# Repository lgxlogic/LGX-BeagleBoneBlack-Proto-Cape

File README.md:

BeagleBone Black Proto Cape
===========================

This repository contains the Eagle design files for the LGX Proto Cape for the BeagleBone Black.  

Check out the LGX Proto Cape at http://www.logicsupply.com/products/cbb_proto  

**NOTE**: On CBB-Proto r01 the **SYS5V** and **VDD5V** labels are reversed. This is only
a concern if drawing higher currents from the 5V rail, or when supplying power 
to the BeagleBone through the proto cape instead of the DC barrel jack. In 
both cases the bus labelled **SYS5V** should be used, as it is connected directly 
to the BeagleBone's DC input.  

----

Follow us on Google+ for updates and more information: https://plus.google.com/u/0/b/103613886667848850929/

Created by Alexander Hiam for LGX / Logic Supply.

Creative Commons Attribution 3.0 Unported License.  
To view a copy of this license,visit http://creativecommons.org/licenses/by/3.0/.  
All text above must be included in any redistribution.

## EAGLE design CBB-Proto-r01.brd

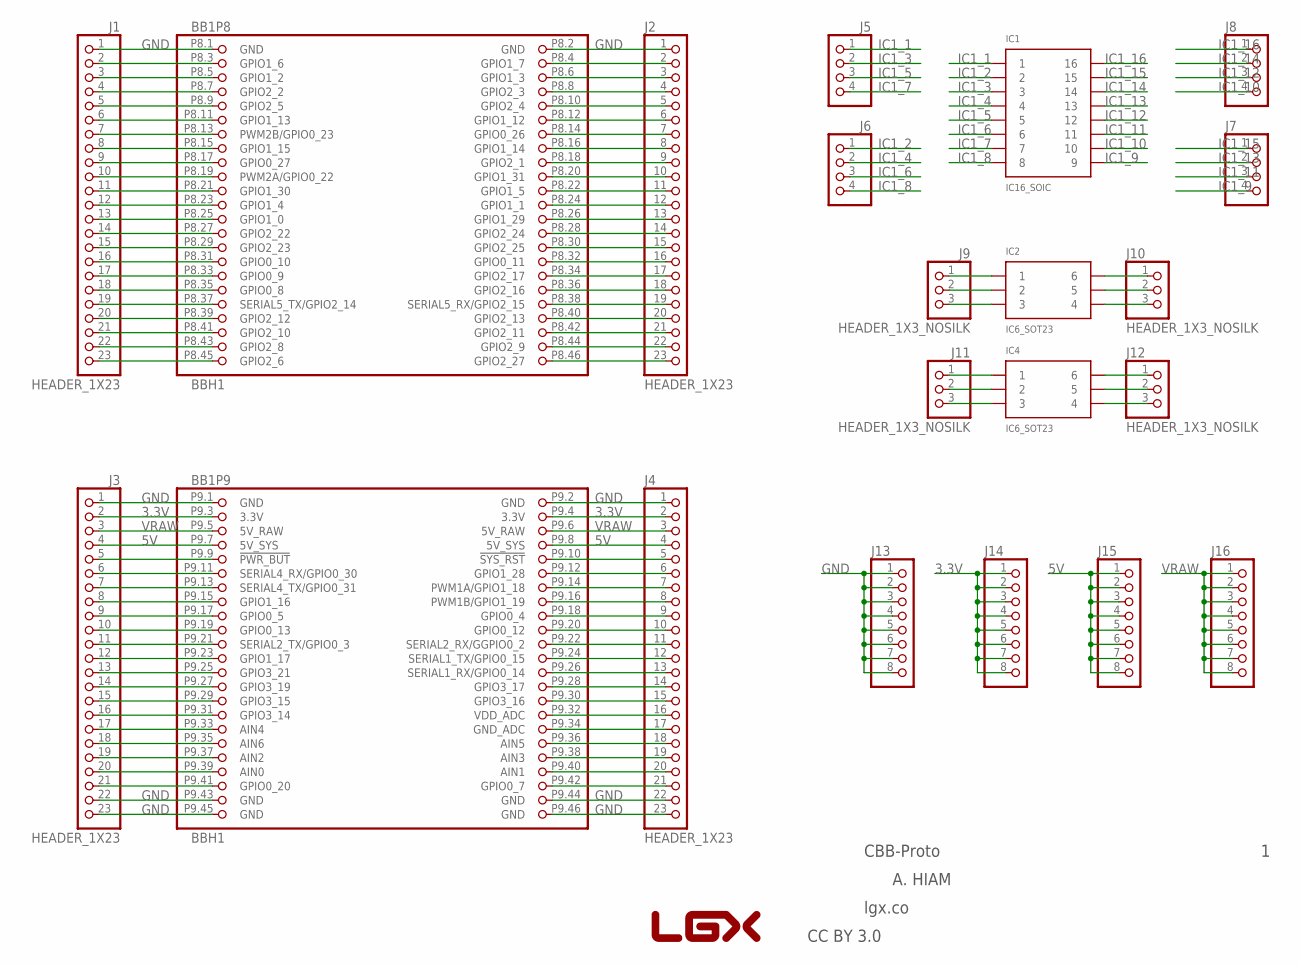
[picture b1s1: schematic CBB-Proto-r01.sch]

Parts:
BB1: BBH1; BB_CAPE
IC1: IC16_SOIC; SOIC16
IC2, IC4: IC6_SOT23; SOT23-6
J1, J2, J3, J4: HEADER_1X23
J5, J6, J7, J8: HEADER_1X4
J9, J10, J11, J12: HEADER_1X3_NOSILK
J13, J14, J15, J16: HEADER_1X8
U$1: LOGO-LGX

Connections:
3.3V: BB1.P9.3 (3.3V), BB1.P9.4 (3.3V), J3.2, J4.2, J14.1, J14.2, J14.3, J14.4, J14.5, J14.6, J14.7, J14.8
5V: BB1.P9.7 (5V_SYS), BB1.P9.8 (5V_SYS), J3.4, J4.4, J15.1, J15.2, J15.3, J15.4, J15.5, J15.6, J15.7, J15.8
GND: BB1.P8.1 (GND), BB1.P8.2 (GND), BB1.P9.1 (GND), BB1.P9.2 (GND), BB1.P9.43 (GND), BB1.P9.44 (GND), BB1.P9.45 (GND), BB1.P9.46 (GND), J1.1, J2.1, J3.1, J3.22, J3.23, J4.1, J4.22, J4.23, J13.1, J13.2, J13.3, J13.4, J13.5, J13.6, J13.7, J13.8
IC1_1: IC1.1, J5.1
IC1_2: IC1.2, J6.1
IC1_3: IC1.3, J5.2
IC1_4: IC1.4, J6.2
IC1_5: IC1.5, J5.3
IC1_6: IC1.6, J6.3
IC1_7: IC1.7, J5.4
IC1_8: IC1.8, J6.4
IC1_9: IC1.9, J7.4
IC1_10: IC1.10, J8.4
IC1_11: IC1.11, J7.3
IC1_12: IC1.12, J8.3
IC1_13: IC1.13, J7.2
IC1_14: IC1.14, J8.2
IC1_15: IC1.15, J7.1
IC1_16: IC1.16, J8.1
unnamed: BB1.P8.4 (GPIO1_7), J2.2
unnamed: BB1.P8.6 (GPIO1_3), J2.3
unnamed: BB1.P8.8 (GPIO2_3), J2.4
unnamed: BB1.P8.10 (GPIO2_4), J2.5
unnamed: BB1.P8.12 (GPIO1_12), J2.6
unnamed: BB1.P8.14 (GPIO0_26), J2.7
unnamed: BB1.P8.16 (GPIO1_14), J2.8
unnamed: BB1.P8.18 (GPIO2_1), J2.9
unnamed: BB1.P8.20 (GPIO1_31), J2.10
unnamed: BB1.P8.22 (GPIO1_5), J2.11
unnamed: BB1.P8.24 (GPIO1_1), J2.12
unnamed: BB1.P8.26 (GPIO1_29), J2.13
unnamed: BB1.P8.28 (GPIO2_24), J2.14
unnamed: BB1.P8.30 (GPIO2_25), J2.15
unnamed: BB1.P8.32 (GPIO0_11), J2.16
unnamed: BB1.P8.34 (GPIO2_17), J2.17
unnamed: BB1.P8.36 (GPIO2_16), J2.18
unnamed: BB1.P8.38 (SERIAL5_RX/GPIO2_15), J2.19
unnamed: BB1.P8.40 (GPIO2_13), J2.20
unnamed: BB1.P8.42 (GPIO2_11), J2.21
unnamed: BB1.P8.44 (GPIO2_9), J2.22
unnamed: BB1.P8.46 (GPIO2_27), J2.23
unnamed: BB1.P8.45 (GPIO2_6), J1.23
unnamed: BB1.P8.43 (GPIO2_8), J1.22
unnamed: BB1.P8.41 (GPIO2_10), J1.21
unnamed: BB1.P8.39 (GPIO2_12), J1.20
unnamed: BB1.P8.37 (SERIAL5_TX/GPIO2_14), J1.19
unnamed: BB1.P8.35 (GPIO0_8), J1.18
unnamed: BB1.P8.33 (GPIO0_9), J1.17
unnamed: BB1.P8.31 (GPIO0_10), J1.16
unnamed: BB1.P8.29 (GPIO2_23), J1.15
unnamed: BB1.P8.27 (GPIO2_22), J1.14
unnamed: BB1.P8.25 (GPIO1_0), J1.13
unnamed: BB1.P8.23 (GPIO1_4), J1.12
unnamed: BB1.P8.21 (GPIO1_30), J1.11
unnamed: BB1.P8.19 (PWM2A/GPIO0_22), J1.10
unnamed: BB1.P8.17 (GPIO0_27), J1.9
unnamed: BB1.P8.15 (GPIO1_15), J1.8
unnamed: BB1.P8.13 (PWM2B/GPIO0_23), J1.7
unnamed: BB1.P8.11 (GPIO1_13), J1.6
unnamed: BB1.P8.9 (GPIO2_5), J1.5
unnamed: BB1.P8.7 (GPIO2_2), J1.4
unnamed: BB1.P8.5 (GPIO1_2), J1.3
unnamed: BB1.P8.3 (GPIO1_6), J1.2
unnamed: BB1.P9.41 (GPIO0_20), J3.21
unnamed: BB1.P9.39 (AIN0), J3.20
unnamed: BB1.P9.37 (AIN2), J3.19
unnamed: BB1.P9.35 (AIN6), J3.18
unnamed: BB1.P9.33 (AIN4), J3.17
unnamed: BB1.P9.31 (GPIO3_14), J3.16
unnamed: BB1.P9.29 (GPIO3_15), J3.15
unnamed: BB1.P9.27 (GPIO3_19), J3.14
unnamed: BB1.P9.25 (GPIO3_21), J3.13
unnamed: BB1.P9.23 (GPIO1_17), J3.12
unnamed: BB1.P9.21 (SERIAL2_TX/GPIO0_3), J3.11
unnamed: BB1.P9.19 (GPIO0_13), J3.10
unnamed: BB1.P9.17 (GPIO0_5), J3.9
unnamed: BB1.P9.15 (GPIO1_16), J3.8
unnamed: BB1.P9.13 (SERIAL4_TX/GPIO0_31), J3.7
unnamed: BB1.P9.11 (SERIAL4_RX/GPIO0_30), J3.6
unnamed: BB1.P9.9 (!PWR_BUT), J3.5
unnamed: BB1.P9.10 (!SYS_RST), J4.5
unnamed: BB1.P9.12 (GPIO1_28), J4.6
unnamed: BB1.P9.14 (PWM1A/GPIO1_18), J4.7
unnamed: BB1.P9.16 (PWM1B/GPIO1_19), J4.8
unnamed: BB1.P9.18 (GPIO0_4), J4.9
unnamed: BB1.P9.20 (GPIO0_12), J4.10
unnamed: BB1.P9.22 (SERIAL2_RX/GGPIO0_2), J4.11
unnamed: BB1.P9.24 (SERIAL1_TX/GPIO0_15), J4.12
unnamed: BB1.P9.26 (SERIAL1_RX/GPIO0_14), J4.13
unnamed: BB1.P9.28 (GPIO3_17), J4.14
unnamed: BB1.P9.30 (GPIO3_16), J4.15
unnamed: BB1.P9.32 (VDD_ADC), J4.16
unnamed: BB1.P9.34 (GND_ADC), J4.17
unnamed: BB1.P9.36 (AIN5), J4.18
unnamed: BB1.P9.38 (AIN3), J4.19
unnamed: BB1.P9.40 (AIN1), J4.20
unnamed: BB1.P9.42 (GPIO0_7), J4.21
unnamed: IC2.1, J9.1
unnamed: IC2.2, J9.2
unnamed: IC2.3, J9.3
unnamed: IC2.6, J10.1
unnamed: IC2.5, J10.2
unnamed: IC2.4, J10.3
unnamed: IC4.1, J11.1
unnamed: IC4.2, J11.2
unnamed: IC4.3, J11.3
unnamed: IC4.6, J12.1
unnamed: IC4.5, J12.2
unnamed: IC4.4, J12.3
VRAW: BB1.P9.5 (5V_RAW), BB1.P9.6 (5V_RAW), J3.3, J4.3, J16.1, J16.2, J16.3, J16.4, J16.5, J16.6, J16.7, J16.8

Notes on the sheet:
A. HIAM
CBB-Proto
lgx.co
CC BY 3.0

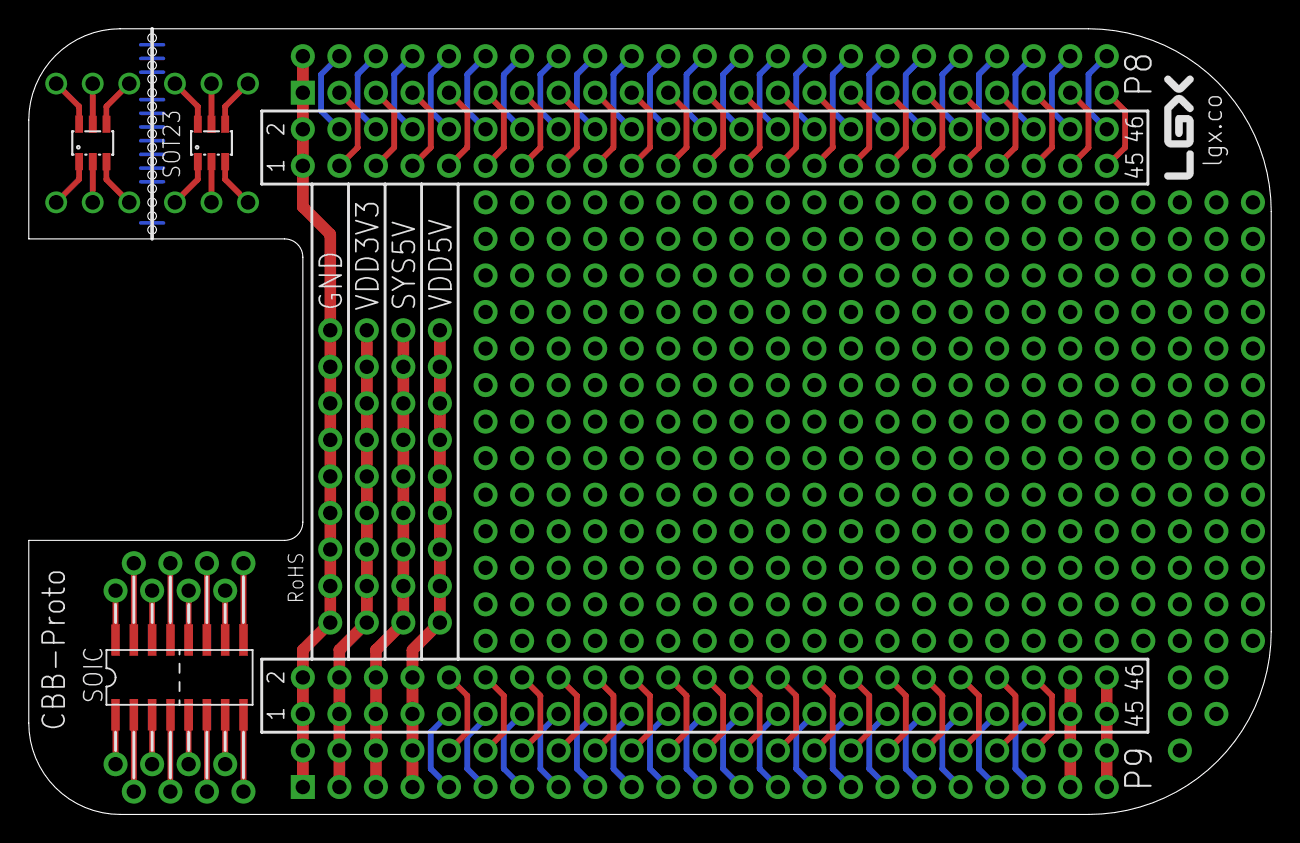
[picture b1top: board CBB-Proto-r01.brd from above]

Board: 2 copper layers, 86.4 x 54.6 mm, 21 parts (0 on the bottom side), 110 nets.

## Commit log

2013-07-09 added Eagle design files
2013-07-26 revert to r01
2013-08-23 description and licensing
2013-08-23 link to logicsupply.com
2013-08-23 link to product page
2013-08-28 added schematic and layout PDFs
2014-06-06 added note about reversed SYS5V and VDD5V labels
2014-06-06 formatting
